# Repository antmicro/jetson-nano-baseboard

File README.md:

# Jetson Nano Baseboard

Copyright (c) 2020-2025 [Antmicro](https://www.antmicro.com)

## Overview

This project contains open hardware design files for a baseboard supporting the NVIDIA Jetson Nano, Xavier NX and TX2 NX SoMs.
It was created by [Antmicro](https://antmicro.com), a custom hardware, software and AI engineering company and NVIDIA's Jetson ecosystem partner.
The board can be interfaced with MIPI CSI-2 video devices through a unified Flexible Flat Cable (FFC) connector, supporting up to 4 sensors in a 2-lane configuration or 3 sensors in a 4-lane configuration.
Please refer to the Product Design Guide for the relevant SoM for more details regarding the supported CSI lane mappings.
You will find the SoM-related resources in NVIDIA's [Jetson Download Center](https://developer.nvidia.com/embedded/downloads). 

The design files for this project starting from Rev. 1.5 are provided and maintained in KiCad.
Older revisions of the board were prepared in Altium Designer and are kept on a separate [branch](https://github.com/antmicro/jetson-nano-baseboard/tree/1.4.7-altium).

### Project structure:

The main directory contains the KiCad design files, LICENSE and README.
The remaining files are stored in the following directories:

* ``img`` - contains graphics for this README
* ``linux-patches`` - contains patches which add camera support for camera modules from Allied Vision (see the BSP section below)

## Key features

* Jetson Nano / Xavier NX / TX2 NX SO-DIMM connector
* Gigabit Ethernet RJ45 connector
* Micro USB debug connector
* USB-C DFP (Host) port
* Micro HDMI video output interface
* Mini DisplayPort video output interface
* 2x 50-pin FFC connectors exposing up to 4 MIPI CSI-2 camera interfaces
* M.2 (key M) connector exposing PCIe x4 interface
* RTC battery backup
* EEPROM for storing board ID/SN
* 100x55mm (3.93 x 2.16 inch) mechanical outline 

## Getting started

The board can be produced and assembled using the provided design files.
Please take a look at the mechanical layers for more information regarding the PCB stackup recommended for fabrication.
The board can be powered by a voltage in the 6-36VDC range.
It is recommended to use a 12V 2A DC supply to power the board.
The board has an integrated power sequencer that starts the module automatically right after applying power supply.

### BSP

The baseboard's I/O interfaces are supported in the standard [Linux for Tegra (L4T) BSPs](https://developer.nvidia.com/embedded/linux-tegra) provided by NVIDIA for Jetson Nano / Xavier NX / TX2 NX. 
The BSP should work with the Open Source Jetson Baseboard out of the box.
However, to use the baseboard with various cameras and other accessories you may need to make modifications.
If you plan to use the board with Allied Vision [Alvium](https://www.alliedvision.com/en/products/embedded-vision-solutions/alvium-camera-modules-for-embedded-and-machine-vision-applications.html) image sensors, there is a ``linux-patches`` directory, which contains patch files that add support for the Allied Vision cameras for this baseboard with the Jetson Nano NX module.
The patches are named with the L4T release and can be applied to the corresponding branches of the Linux [repository](https://github.com/alliedvision/linux_nvidia_jetson) released by Allied Vision. 
Antmicro's services involve BSP development so you can hire us to make the necessary modifications for you.

You can use the USB OTG interface connector to upload a BSP image to a SoM inserted into the baseboard.

### Debug UART connection

Most of the debug messages are provided through the serial console.
The board includes an FTDI chip providing the UART interface to the host PC.
Please refer to the schematic sheets for more details.
The default debug UART channel is accessible through ``/dev/ttyUSB0`` (assuming that there are no other FTDI units connected to your PC).
The default baudrate for serial debug connection is 115200 baud with an 8-bit transmission, 1 stop bit and with no flow control.

### Revision info

1.5.x revision includes the design files converted into KiCad.
The BOM has been altered so the board can be produced despite the global chip shortage situation.
Revision 1.5.x changes the I2C multiplexer (PCA9548 -> PCA9547) used for handling the cameras and video accessories. 
You may need to adjust the devicetree entries for video accessories to make them work with the new I2C multiplexer chip.

## License

This project is licensed under the [Apache-2.0](LICENSE) license.

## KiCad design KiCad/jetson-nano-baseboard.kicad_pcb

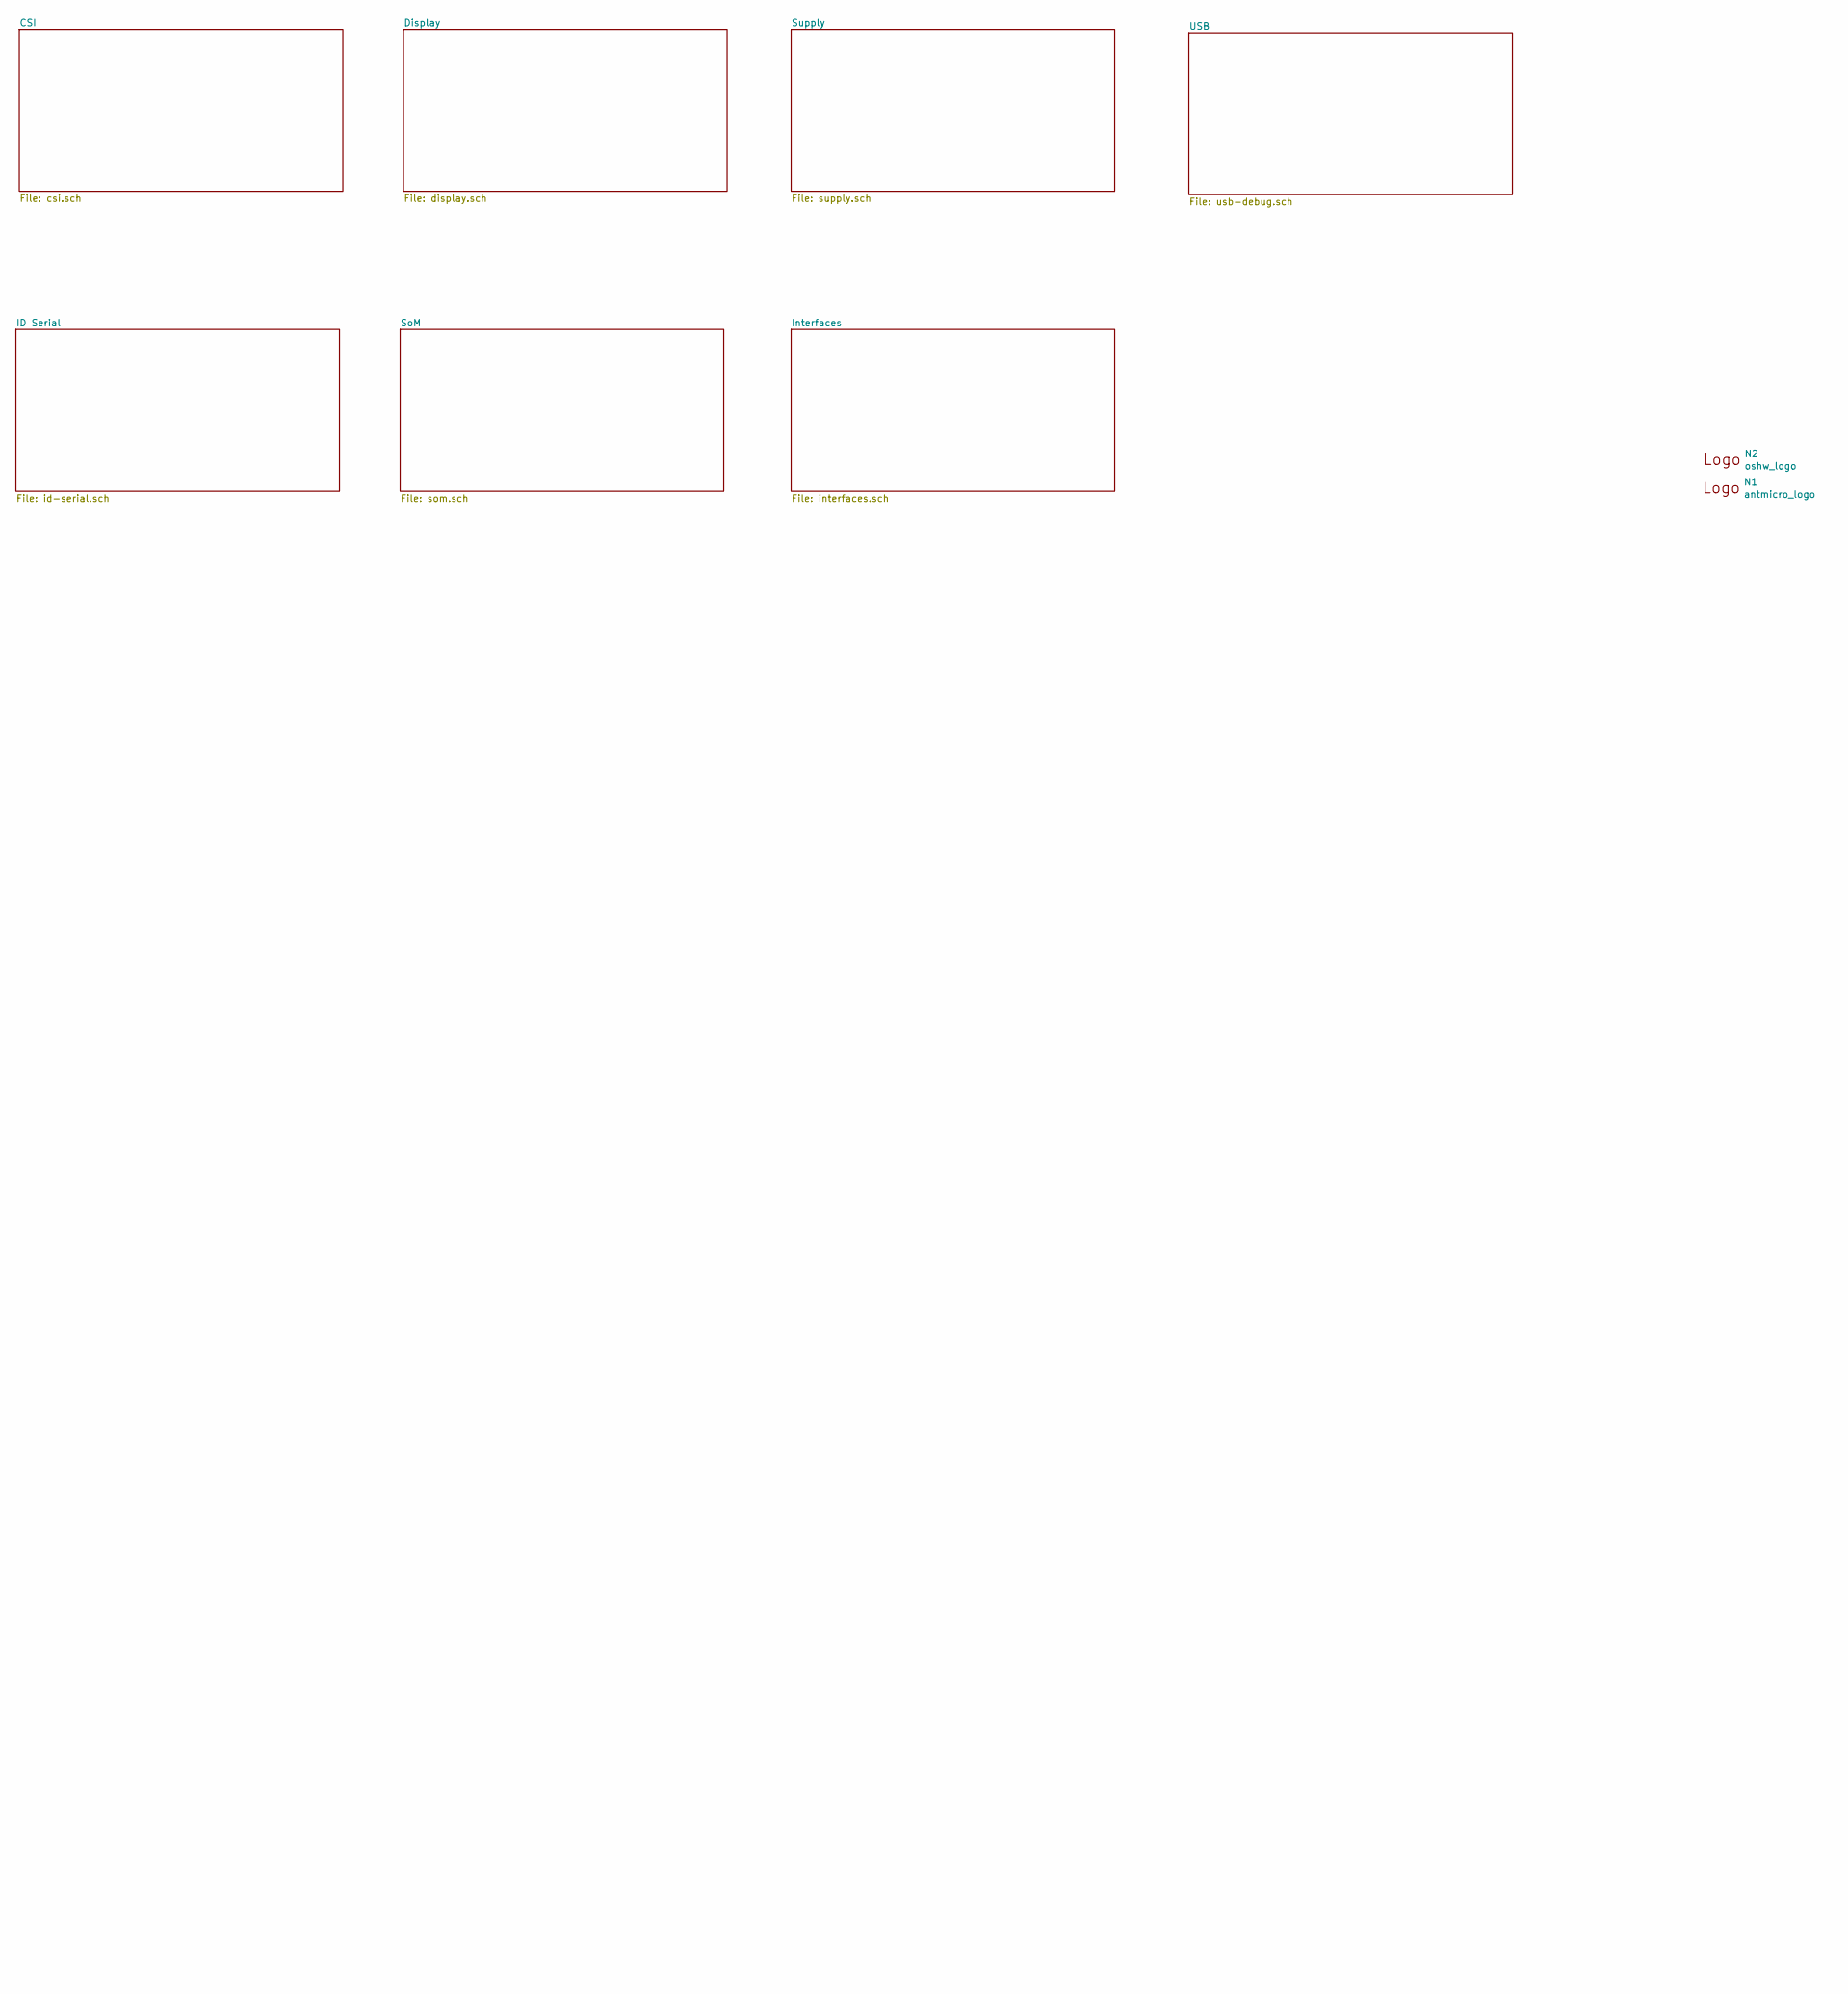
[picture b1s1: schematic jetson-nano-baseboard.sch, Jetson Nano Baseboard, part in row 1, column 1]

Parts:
N1: antmicro_logo; antmicro-logo_scaled_15mm
N2: oshw_logo; oshw-logo

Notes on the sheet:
Text

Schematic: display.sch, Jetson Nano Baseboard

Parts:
C1, C2, C3, C4: C_4u7_0402; 0402-cap; MPN GRM155R61A475MEAAD
C5, C6, C7, C8, C12, C26, C27, C39, C40, C42, C43, C44, C45, C73, C74, C75, C76, C77, C78, C79, C80: C_100n_0402; 0402-cap; MPN 0402X104K6R3CT
D2, D4: 1N4148WS; SOD-323; MPN 1N4148WS
D10, D11, D12: TPD2E009DBZR; SOT-23s; MPN TPD2E009DBZR
IC2, IC18: SON-15; PartSymbol TPD8S009DSMR
IC6: PCA9517ADP; MSOP-8; MPN PCA9517ADP
IC11: SN74LV1T125DCKR; SC70-5; MPN SN74LV1T125DCKR
J1: 685119136923; WE_685119136923; MPN 685119136923
J2: 2129320-3; MPN 2309413-1
L8, L9, L10: BLM18SG121TN1D; 0603; MPN BLM18SG121TN1D
M1: jetson-nano-connector; PartSymbol 2309413-1
R1, R2, R3, R4, R7, R8, R9, R10: R_5R6_0402; 0402-res; MPN ERJ2GEJ5R6X
R5, R6, R11, R37, R81, R83, R88: R_2k_0402; 0402-res; MPN CRCW04022K00FKED
R12, R82, R98, R99: R_0R_0402; 0402-res; MPN ERJ2GE0R00X
R26, R30, R100: R_100k_0402; 0402-res; MPN CRCW0402100KFKEDHP
R31, R32: R_1M0_0402; 0402-res; MPN CRG0402F1M0
T1: BSS138APW; SC70-3; MPN BSS138PW
TP2, TP13, TP14, TP25, TP26, TP33, TP34: TP-R-1.5; MPN N/A

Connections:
1V8_SYS: C5.1, IC11.5 (VCC), R88.1; also elsewhere on the board
3V3_SYS: C26.1, IC6.1 (VCCA), L10.1, R11.1, R81.1; also elsewhere on the board
5V0_SYS: IC2.13 (VCC), IC2.15 (VCC), L9.1; also elsewhere on the board
/Display/DP_CEC: J2.6 (CONFIG2), R32.2
/Display/DP_HPD: IC11.4 (Y), M1.88 (DP0_HPD)
/Display/DP_HPD_IN: D12.2 (IO2), IC11.2 (A), J2.2 (HOTPLUG), R100.2
/Display/DP_MODE: J2.4 (CONFIG1), R31.2
/Display/EDP0_TX_N: C40.1, M1.39 (DP0_TXD0_N)
/Display/EDP0_TX_P: C39.1, M1.41 (DP0_TXD0_P)
/Display/EDP1_TX_N: C43.1, M1.45 (DP0_TXD1_N)
/Display/EDP1_TX_P: C42.1, M1.47 (DP0_TXD1_P)
/Display/EDP2_TX_N: C7.1, M1.51 (DP0_TXD2_N)
/Display/EDP2_TX_P: C6.1, M1.53 (DP0_TXD2_P)
/Display/EDP3_TX_N: C12.1, M1.57 (DP0_TXD3_N)
/Display/EDP3_TX_P: C8.1, M1.59 (DP0_TXD3_P)
/Display/EDP_AUX_N: C45.1, M1.90 (DP0_AUX_N)
/Display/EDP_AUX_P: C44.1, M1.92 (DP0_AUX_P)
/Display/EDP_C_AUX_C_N: C45.2, J2.18 (AUX_CH_N), R26.1
/Display/EDP_C_AUX_C_P: C44.2, J2.16 (AUX_CH_P), R30.2
/Display/ML_C_LANE0_N: C40.2, IC2.3 (D0-), J2.5 (ML_LANE0_N)
/Display/ML_C_LANE0_P: C39.2, IC2.1 (D0+), J2.3 (ML_LANE0_P)
/Display/ML_C_LANE1_N: C43.2, IC2.6 (D1-), J2.11 (ML_LANE1_N)
/Display/ML_C_LANE1_P: C42.2, IC2.4 (D1+), J2.9 (ML_LANE1_P)
/Display/ML_C_LANE2_N: C7.2, IC2.9 (D2-), J2.17 (ML_LANE2_N)
/Display/ML_C_LANE2_P: C6.2, IC2.7 (D2+), J2.15 (ML_LANE2_P)
/Display/ML_C_LANE3_N: C12.2, IC2.12 (D3-), J2.12 (ML_LANE3_N)
/Display/ML_C_LANE3_P: C8.2, IC2.10 (D3+), J2.10 (ML_LANE3_P)
/Display/TMDS_C1_CLK_N: C80.2, IC18.12 (D3-), R10.1
/Display/TMDS_C1_CLK_P: C78.2, IC18.10 (D3+), R9.1
/Display/TMDS_C1_D0_N: C79.2, IC18.9 (D2-), R8.1
/Display/TMDS_C1_D0_P: C76.2, IC18.7 (D2+), R7.1
/Display/TMDS_C1_D1_N: C77.2, IC18.6 (D1-), R4.1
/Display/TMDS_C1_D1_P: C75.2, IC18.4 (D1+), R3.1
/Display/TMDS_C1_D2_N: C74.2, IC18.3 (D0-), R2.1
/Display/TMDS_C1_D2_P: C73.2, IC18.1 (D0+), R1.1
/Display/TMDS_CEC: M1.94 (HDMI_CEC), TP26.1
/Display/TMDS_CEC_IN: D11.2 (IO2), J1.14 (CEC), R37.1
/Display/TMDS_CLK_C_N: J1.12 (TMDSClock-), R10.2
/Display/TMDS_CLK_C_P: J1.11 (TMDSClock+), R9.2
/Display/TMDS_CLK_N: C80.1, M1.81 (DP1_TXD3_N)
/Display/TMDS_CLK_P: C78.1, M1.83 (DP1_TXD3_P)
/Display/TMDS_D0_C_N: J1.9 (TMDSData0-), R8.2
/Display/TMDS_D0_C_P: J1.8 (TMDSData0+), R7.2
/Display/TMDS_D0_N: C79.1, M1.75 (DP1_TXD2_N)
/Display/TMDS_D0_P: C76.1, M1.77 (DP1_TXD2_P)
/Display/TMDS_D1_C_N: J1.6 (TMDSData1-), R4.2
/Display/TMDS_D1_C_P: J1.5 (TMDSData1+), R3.2
/Display/TMDS_D1_N: C77.1, M1.69 (DP1_TXD1_N)
/Display/TMDS_D1_P: C75.1, M1.71 (DP1_TXD1_P)
/Display/TMDS_D2_C_N: J1.3 (TMDSData2-), R2.2
/Display/TMDS_D2_C_P: J1.2 (TMDSData2+), R1.2
/Display/TMDS_D2_N: C74.1, M1.63 (DP1_TXD0_N)
/Display/TMDS_D2_P: C73.1, M1.65 (DP1_TXD0_P)
/Display/TMDS_HPD_IN: D11.1 (IO1), J1.19 (HotPlugDetect/HEAC-), R82.1
/Display/TMDS_SCL: M1.100 (DP1_AUX_P), R98.2, TP33.1
/Display/TMDS_SCL_5V0: D10.2 (IO2), IC6.7 (SCLB), J1.15 (SCL), R5.2
/Display/TMDS_SDA: M1.98 (DP1_AUX_N), R99.2, TP34.1
/Display/TMDS_SDA_5V0: D10.1 (IO1), IC6.6 (SDAB), J1.16 (SDA), R6.2
DP_PWR: D2.A, L10.2, R26.2
HDMI_PWR: C27.2, D4.A, IC6.5 (EN), IC6.8 (VCCB), IC18.13 (VCC), IC18.15 (VCC), L9.2, R5.1, R6.1
HDMI_SHIELD: J1.1 (TMDSData2Shield), J1.4 (TMDSData1Shield), J1.7 (TMDSData0Shield), J1.10 (TMDSClockShield), J1.Shell (Shield), L8.2
M2_ALERT: M1.212 (GPIO10), TP2.1; also elsewhere on the board
unnamed: C1.2, C2.2, D4.C, J1.18 (+5VPower)
unnamed: C3.2, C4.2, D2.C, J2.20 (DP_PWR)
unnamed: IC6.2 (SCLA), R81.2, R98.1
unnamed: IC6.3 (SDAA), R11.2, R99.1
unnamed: J1.13 (DDC/CECGround/HEACShield), R12.2
unnamed: M1.206 (GPIO07), TP13.1
unnamed: M1.218 (GPIO12), TP14.1
unnamed: R82.2, R83.1, T1.1 (G)
OTG_USB_VBUS: M1.87 (GPIO00); also elsewhere on the board
TMDS_HPD: M1.96 (DP1_HPD), R88.2, T1.3 (D), TP25.1

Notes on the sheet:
HDMI Interface
5V0
3V3
DDC/HPD
Text
Display
DisplayPort Interface
1V8

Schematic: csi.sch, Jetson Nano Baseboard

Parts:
C9: C_100n_0402; 0402-cap; MPN 0402X104K6R3CT
IC1: TCA9548ARGER; VQFN-24; MPN TCA9548ARGER
J6: WE_68715014522; WE_68715014522_ONE-SIDE; MPN 68715014522
J7: WE_68715014022; MPN 68715014022
M1: jetson-nano-connector; PartSymbol 2309413-1
R13, R15, R17, R19, R21, R23, R39, R57, R58, R59, R60, R61, R78, R79, R80: R_0R_0402; 0402-res; MPN ERJ2GE0R00X
R18, R22, R24, R25, R27, R28, R29, R33, R34, R35: R_2k_0402; 0402-res; MPN CRCW04022K00FKED
TP1, TP3, TP4, TP6, TP9, TP10, TP11, TP12: TP-R-1.5; MPN N/A

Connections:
1V8_SYS: R23.2, R79.2; also elsewhere on the board
3V3_FFC1: J6.47, J6.48, R78.2; also elsewhere on the board
3V3_FFC2: J7.47, J7.48, R80.2; also elsewhere on the board
3V3_SYS: C9.1, IC1.21 (VCC), R34.1, R35.1, R39.2; also elsewhere on the board
5V0_SYS: J6.49, J6.50, J7.49, J7.50; also elsewhere on the board
/CSI/CAM0_SCL: J6.40, R15.1, R24.2
/CSI/CAM0_SDA: J6.39, R13.1, R25.2
/CSI/CAM1_SCL: J6.42, R18.2, R21.1
/CSI/CAM1_SDA: J6.41, R17.1, R22.2
/CSI/CAM2_SCL: J7.42, R27.2, R58.1
/CSI/CAM2_SDA: J7.41, R19.1, R28.2
/CSI/CAM3_SCL: J7.40, R33.2, R61.1
/CSI/CAM3_SDA: J7.39, R29.2, R59.1
/CSI/CAM_I2C_SCL: M1.213 (CAM_I2C_SCL), R35.2, R60.2, TP10.1
/CSI/CAM_I2C_SDA: M1.215 (CAM_I2C_SDA), R34.2, R57.2, TP1.1
/CSI/CSI_A_CLK_N: J7.28, M1.10 (CSI0_CLK_N)
/CSI/CSI_A_CLK_P: J7.29, M1.12 (CSI0_CLK_P)
/CSI/CSI_A_D0_N: J7.25, M1.4 (CSI0_D0_N)
/CSI/CSI_A_D0_P: J7.26, M1.6 (CSI0_D0_P)
/CSI/CSI_A_D1_N: J7.23, M1.16 (CSI0_D1_N)
/CSI/CSI_A_D1_P: J7.24, M1.18 (CSI0_D1_P)
/CSI/CSI_B_D0_N: J7.21, M1.3 (CSI1_D0_N)
/CSI/CSI_B_D0_P: J7.22, M1.5 (CSI1_D0_P)
/CSI/CSI_B_D1_N: J7.19, M1.15 (CSI1_D1_N)
/CSI/CSI_B_D1_P: J7.20, M1.17 (CSI1_D1_P)
/CSI/CSI_C_CLK_N: J7.10, M1.52 (CSI4_CLK_N)
/CSI/CSI_C_CLK_P: J7.11, M1.54 (CSI4_CLK_P)
/CSI/CSI_C_D0_N: J7.7, M1.46 (CSI4_D0_N)
/CSI/CSI_C_D0_P: J7.8, M1.48 (CSI4_D0_P)
/CSI/CSI_C_D1_N: J7.5, M1.58 (CSI4_D1_N)
/CSI/CSI_C_D1_P: J7.6, M1.60 (CSI4_D1_P)
/CSI/CSI_D_D0_N: J7.3, M1.40 (CSI4_D2_N)
/CSI/CSI_D_D0_P: J7.4, M1.42 (CSI4_D2_P)
/CSI/CSI_D_D1_N: J7.1, M1.64 (CSI4_D3_N)
/CSI/CSI_D_D1_P: J7.2, M1.66 (CSI4_D3_P)
/CSI/CSI_E_CLK_N: J6.28, M1.28 (CSI2_CLK_N)
/CSI/CSI_E_CLK_P: J6.29, M1.30 (CSI2_CLK_P)
/CSI/CSI_E_D0_N: J6.25, M1.22 (CSI2_D0_N)
/CSI/CSI_E_D0_P: J6.26, M1.24 (CSI2_D0_P)
/CSI/CSI_E_D1_N: J6.23, M1.34 (CSI2_D1_N)
/CSI/CSI_E_D1_P: J6.24, M1.36 (CSI2_D1_P)
/CSI/CSI_F_CLK_N: M1.27 (CSI3_CLK_N)
/CSI/CSI_F_CLK_P: M1.29 (CSI3_CLK_P)
/CSI/CSI_F_D0_N: J6.21, M1.21 (CSI3_D0_N)
/CSI/CSI_F_D0_P: J6.22, M1.23 (CSI3_D0_P)
/CSI/CSI_F_D1_N: J6.19, M1.33 (CSI3_D1_N)
/CSI/CSI_F_D1_P: J6.20, M1.35 (CSI3_D1_P)
/CSI/CSI_G_CLK_N: J6.10, M1.76 (DSI_CLK_N)
/CSI/CSI_G_CLK_P: J6.11, M1.78 (DSI_CLK_P)
/CSI/CSI_G_D0_N: J6.7, M1.70 (DSI_D0_N)
/CSI/CSI_G_D0_P: J6.8, M1.72 (DSI_D0_P)
/CSI/CSI_G_D1_N: J6.5, M1.82 (DSI_D1_N)
/CSI/CSI_G_D1_P: J6.6, M1.84 (DSI_D1_P)
unnamed: IC1.1 (SD0), R13.2
unnamed: IC1.2 (SC0), R15.2
unnamed: IC1.3 (SD1), R17.2
unnamed: IC1.4 (SC1), R21.2
unnamed: IC1.5 (SD2), R19.2
unnamed: IC1.6 (SC2), R58.2
unnamed: IC1.7 (SD3), R59.2
unnamed: IC1.8 (SC3), R61.2
unnamed: IC1.10 (SD4), TP11.1
unnamed: IC1.11 (SC4), TP12.1
unnamed: IC1.19 (SCL), R60.1
unnamed: IC1.20 (SDA), R57.1
unnamed: IC1.24 (~RESET), R39.1
unnamed: M1.9 ((CSI1_CLK)RSVD), TP3.1
unnamed: M1.11 ((CSI1_CLK)RSVD), TP4.1
unnamed: M1.118 (GPIO01), TP9.1
unnamed: M1.120 (CAM1_PWDN), TP6.1
unnamed: R18.1, R22.1, R23.1, R24.1, R25.1, R78.1
unnamed: R27.1, R28.1, R29.1, R33.1, R79.1, R80.1
VSYNC_CAM1_1: J6.32; also elsewhere on the board
VSYNC_CAM1_2: J6.34; also elsewhere on the board
VSYNC_CAM2_1: J7.32, M1.114 (CAM0_PWDN)
VSYNC_CAM2_2: J7.34; also elsewhere on the board

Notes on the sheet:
CAM_L_D3_N
CAM_L_D3_P
CAM_L_D2_N
CAM_L_D2_P
CAM_L_D1_N
CAM_L_D1_P
CAM_L_D0_N
CAM_L_D0_P
CAM_L_SDA
CAM_L_SCL
CAM_R_SDA
CAM_R_SCL
CAM_L_CLK_N
CAM_L_CLK_P
LEFT CAMERA
CAM_R_D3_N
CAM_R_D3_P
CAM_R_D2_N
CAM_R_D2_P
CAM_R_D1_N
CAM_R_D1_P
CAM_R_D0_N
CAM_R_D0_P
CAM_R_CLK_N
CAM_R_CLK_P
RIGHT CAMERA
Camera FFC #1
Camera FFC #2
0x70h
0b1110000R
I2C address:
SoM interface
Text
Camera I2C multiplexer
Camera Interfaces

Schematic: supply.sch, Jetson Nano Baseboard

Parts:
C16, C17, C18: C_47u_0805; 0805-cap; MPN C0805C476M9PACTU
C19, C71: C_100n_0402; 0402-cap; MPN 0402X104K6R3CT
C21, C22, C23: C_2u2_1206; 1206-cap; MPN C1206C225M4VACTU
C24: C_10n_0402; 0402-cap; MPN 04025G103ZAT2A
C25: C_4n7_0402; 0402-cap; MPN CGA2B3X7S2A472K050BB
C28: C_1u_0402; 0402-cap; MPN C1005X6S1A105K050BC
C41: C_47n_0402; 0402-cap; MPN MC0402X473K160CT
C55, C57, C59, C65: C_2u2_0402; 0402-cap; MPN C1005X5R1A225K050BC
C56, C58, C60, C63: C_10u_0603; 0603-cap; MPN GRM188R61A106KE69D
C61: C_100p_0402; 0402-cap; MPN 0402N101J500CT
C64: C_47p_0402; 0402-cap; MPN C0402C470J5GACTU
D1: PDS760-13; PowerDI; MPN PDS760-13
D13, D14: 1N4148WS; SOD-323; MPN 1N4148WS
FAN1: molex_2223-2021; MPN 2223-2021
IC3: TPS54561; WSON-10_4x4; MPN TPS54561-Q1
IC4: TLV70018DCKT; SC70-5; MPN TLV70018DCKT
IC8, IC9: LM3671MF-3.3; SOT23-5N; MPN LM3671MF-3.3/NOPB
IC10: TPS62823DLCT; TPS62823; MPN TPS62823DLCT
IC12: 74HC00PW; TSSOP-14; MPN 74HC00PW
IC13: SN74LVC1G126DCKR; R-PDSO-G5; MPN SN74LVC1G126DCKR
J4: DC_SOCKET; MPN MJ-179PH
L1: WE_7447798720; MPN 7447798720
L4, L6: LQH32PN2R2NN0L; MPN LQH32PN2R2NN0L
L5: IHLP1212AEERR47M11; IHLP-1212AE; MPN IHLP1212AEERR47M11
R16, R36, R87: R_1k_0402; 0402-res; MPN CR0402-FX-1001GLF
R44, R134: R_243k_0402; 0402-res; MPN MCMR04X2433FTL
R45: R_49R9_0402; 0402-res; MPN CRCW040249R9FKED
R46, R135: R_53k6_0402; 0402-res; MPN CPF0402B53K6E1
R48: R_16k9_0402; 0402-res; MPN ERA2AEB1692X
R52: R_10k2_0402; 0402-res; MPN MCWR04X1022FTL
R75, R89, R91, R92, R130: R_0R_0402; 0402-res; MPN ERJ2GE0R00X
R76, R90, R93, R94, R95, R96: R_10k_0402; 0402-res; MPN CRCW040210K0FKEDHP
R77: R_100k_0402; 0402-res; MPN CRCW0402100KFKEDHP
R84, R86: R_200k_0402; 0402-res; MPN RC0402FR-07200KL
R85: R_470k_0402; 0402-res; MPN RC0402FR-07470KL
T3: BSS138APW; SC70-3; MPN BSS138PW
TP5, TP16, TP17, TP40, TP41, TP42, TP43, TP44, TP45, TP47: TP-R-1.5; MPN N/A

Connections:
1V8_SYS: C28.2, IC4.5 (VOUT), TP47.1; also elsewhere on the board
3V3_FFC1: C58.2, IC9.4 (FB), L6.2, TP45.1; also elsewhere on the board
3V3_FFC2: C56.2, IC8.4 (FB), L4.2, TP43.1; also elsewhere on the board
3V3_SYS: C60.2, C61.2, L5.2, R134.1, TP41.1; also elsewhere on the board
5V0_SYS: C16.2, C17.2, C18.2, C55.2, C57.2, C59.2, C65.2, C71.2, D14.C, FAN1.1, IC4.1 (VIN), IC8.1 (VIN), IC9.1 (VIN), IC10.7 (VIN), IC12.14 (VCC), IC13.1 (OE), IC13.5 (VCC), L1.2, R16.1, R36.1, R45.2, R75.2, R77.2, R84.2, R86.2, R89.2, R91.2, R92.1, TP42.1; also elsewhere on the board
#MOD_SLEEP: R95.2; also elsewhere on the board
#RESET: R76.2, R90.2, R93.2, R94.2, R96.2; also elsewhere on the board
#SHUTDOWN_REQ: IC12.4 (2A), R86.1; also elsewhere on the board
/Supply/Q: D13.C, IC12.3 (~1Y), IC12.5 (2B), R36.2, R85.1
/Supply/QDEL: C63.2, D13.A, IC12.12 (4A), IC12.13 (4B), IC13.2 (A), R85.2, R87.2
/Supply/\~PWR_SET~: C41.2, IC12.1 (1A), R84.1
unnamed: C19.1, IC3.1 (BOOT)
unnamed: C19.2, D1.C, IC3.9 (SW), L1.1
unnamed: C24.1, IC3.4 (SS/TR)
unnamed: C25.2, R48.1
unnamed: C61.1, IC10.2 (FB), R134.2, R135.2
unnamed: C64.2, IC3.7 (COMP), R48.2
unnamed: D14.A, FAN1.2, T3.3 (D)
unnamed: IC3.3 (EN), TP5.1
unnamed: IC3.5 (RT/CLK), R44.1
unnamed: IC3.6 (FB), R46.1, R52.2
unnamed: IC4.3 (EN), R92.2, R94.1
unnamed: IC8.3 (RUN), R89.1, R90.1
unnamed: IC8.6 (SW), L4.1
unnamed: IC9.3 (RUN), R91.1, R93.1
unnamed: IC9.6 (SW), L6.1
unnamed: IC10.1 (EN), R75.1, R76.1
unnamed: IC10.6 (SW), L5.1
unnamed: IC12.2 (1B), IC12.6 (~2Y), R16.2
unnamed: IC12.8 (~3Y), R130.2
unnamed: IC12.9 (3A), IC12.10 (3B), IC12.11 (~4Y)
unnamed: R45.1, R46.2
unnamed: R95.1, R96.1, T3.1 (G)
PWR_EN: IC13.4 (Y), R130.1; also elsewhere on the board
PWR_GOOD: IC3.10 (PWRGD), R77.1, R87.1, TP40.1; also elsewhere on the board
VIN: C21.2, C22.2, C23.2, IC3.2 (VDD), J4.1, TP16.1

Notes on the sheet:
Text
Power input
9...36 VDC
Main DC/DC
Power sequencer
System 3V3
Camera #2 3V3
Camera #1 3V3
System 1V8
FAN 5V
#RESET - fan off only in shutdown
#PWR_RST
Power Supply
Bulk load
5V/5A
TODO: change into locking one

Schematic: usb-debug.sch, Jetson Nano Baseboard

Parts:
C15, C29: C_47p_0402; 0402-cap; MPN C0402C470J5GACTU
C30, C33, C48, C50, C53, C54, C72: C_100n_0402; 0402-cap; MPN 0402X104K6R3CT
C31: 100u; 1206; Voltage 6.3V; MPN C1206C107M9PACTU
C32, C66: C_1u_0402; 0402-cap; MPN C1005X6S1A105K050BC
C34: C_47u_0805; 0805-cap; MPN C0805C476M9PACTU
C35: C_10u_0603; 0603-cap; MPN GRM188R61A106KE69D
C62: C_4u7_0402; 0402-cap; MPN GRM155R61A475MEAAD
C67: C_2u2_0402; 0402-cap; MPN C1005X5R1A225K050BC
D3, D5, D8, D9: TPD2E009DBZR; SOT-23s; MPN TPD2E009DBZR
D6, D7: TPD4E05U06_PASS; PartSymbol TPD4E05U06DQAR
D17: 1N4148WS; SOD-323; MPN 1N4148WS
IC5: QFN-32; PartNumber FT232RQ
IC7: HD3SS3220; RNH0030A; MPN HD3SS3220RNHT
IC15: TLV70018DCKT; SC70-5; MPN TLV70018DCKT
IC16: NCP380HSNAJAAT1G; TSOP-6; MPN NCP380HSNAJAAT1G
J5, J9: CON-Molex-047346-0001; PartSymbol 47346-0001
J11: 632723300011; WE_632723300011; MPN 632723300011
L2, L3: BLM18EG221SN1D; 0603; MPN BLM18EG221SN1D
L7: BLM18SG121TN1D; 0603; MPN BLM18SG121TN1D
LED1: LED0603; MPN KPT-1608SGC
Q1: PMV32UP; SOT-23s; MPN PMV32UP
R20, R41: R_22R_0402; 0402-res; MPN CRCW040222R0FKED
R42, R47, R49, R56, R62, R63, R64, R65, R66, R68, R71, R103, R104, R105, R106, R107, R108, R109, R110: R_0R_0402; 0402-res; MPN ERJ2GE0R00X
R43: R_470R_0402; 0402-res; MPN CRCW0402470RFKED
R50: 10k2; 0402; MPN CPF0402B10K2E1
R51: R_909k_0402; 0402-res; MPN ERJ2RKF9093X
R53, R67: R_200k_0402; 0402-res; MPN RC0402FR-07200KL
R54, R72, R102, R131: R_10k_0402; 0402-res; MPN CRCW040210K0FKEDHP
R55, R69, R70, R73: R_2k_0402; 0402-res; MPN CRCW04022K00FKED
R101: R_100k_0402; 0402-res; MPN CRCW0402100KFKEDHP
T6: BSS138APW; SC70-3; MPN BSS138PW
TP18, TP19, TP21, TP22, TP32: TP-R-1.5; MPN N/A

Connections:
1V8_DBG: C66.2, IC5.1 (VCCIO), IC15.5 (VOUT)
3V3_SYS: C33.1, IC7.8 (VCC33), R53.2, R69.1, R70.1; also elsewhere on the board
5V0_DBG: C67.2, C72.2, D17.C, IC5.19 (VCC), IC15.1 (VIN), IC15.3 (EN), L3.2
5V0_SYS: C32.2, C34.2, D17.A, IC7.30 (VDD5), IC16.1 (IN), Q1.2 (S), R42.1, R43.2, R47.2, R54.1, R55.1, R67.2, R71.1, R101.2; also elsewhere on the board
/USB/CC1: IC7.2 (CC1), R63.1, R66.2
/USB/CC2: IC7.1 (CC2), R64.1, R65.2
/USB/C_CC1: D5.2 (IO2), J11.A5 (CC1), R63.2, R64.2
/USB/C_CC2: D5.1 (IO1), J11.B5 (CC2), R65.1, R66.1
/USB/C_USBSS_RX1_N: D6.1 (CH1), J11.B10 (SSRXn1), R104.2
/USB/C_USBSS_RX1_P: D6.2 (CH2), J11.B11 (SSRXp1), R106.2
/USB/C_USBSS_RX2_N: D7.5 (CH4), J11.A10 (SSRXn2), R109.2
/USB/C_USBSS_RX2_P: D7.4 (CH3), J11.A11 (SSRXp2), R110.2
/USB/C_USBSS_RX6_N: IC7.10 (RXn), R108.2
/USB/C_USBSS_RX6_P: IC7.9 (RXp), R107.2
/USB/C_USBSS_TX1_N: C48.1, D6.5 (CH4), J11.A3 (SSTXn1)
/USB/C_USBSS_TX1_P: C50.1, D6.4 (CH3), J11.A2 (SSTXp1)
/USB/C_USBSS_TX2_N: C53.1, D7.2 (CH2), J11.B3 (SSTXn2)
/USB/C_USBSS_TX2_P: C54.1, D7.1 (CH1), J11.B2 (SSTXp2)
/USB/C_USBSS_TX6_N: IC7.7 (TXn), R105.2
/USB/C_USBSS_TX6_P: IC7.6 (TXp), R103.2
/USB/DBG_USB_D_N: C29.2, D3.1 (IO1), IC5.15 (USBDN), J9.2 (D-)
/USB/DBG_USB_D_P: C15.2, D3.2 (IO2), IC5.14 (USBDP), J9.3 (D+)
/USB/EN_MUX: IC7.12 (ENn_MUX), R56.2, R68.1
/USB/USBC_ADDR: IC7.22 (ADDR), TP21.1
/USB/USBC_FAULT: IC7.24 (VCONN_FAULT_N), TP32.1
/USB/USBC_ID: IC7.27 (ID), Q1.1 (G), R68.2, R101.1, TP18.1
/USB/USBC_INTN: IC7.23 (INT_N/OUT3), R67.1
/USB/USBC_SCL: IC7.26 (SCL/OUT2), R70.2
/USB/USBC_SDA: IC7.25 (SDA/OUT1), R69.2
/USB/USBSS_RX1_N: IC7.14 (RX1n), R104.1
/USB/USBSS_RX1_P: IC7.15 (RX1p), R106.1
/USB/USBSS_RX2_N: IC7.18 (RX2n), R109.1
/USB/USBSS_RX2_P: IC7.19 (RX2p), R110.1
/USB/USBSS_TX1_N: C48.2, IC7.16 (TX1n)
/USB/USBSS_TX1_P: C50.2, IC7.17 (TX1p)
/USB/USBSS_TX2_N: C53.2, IC7.20 (TX2n)
/USB/USBSS_TX2_P: C54.2, IC7.21 (TX2p)
unnamed: C30.2, IC5.16 (3V3OUT)
unnamed: C31.2, IC16.6 (OUT), L2.1
unnamed: C62.2, D9.1 (IO1), D9.2 (IO2), J5.1 (VCC), R71.2, R72.1
unnamed: IC5.2 (RXD), R41.1
unnamed: IC5.30 (TXD), R20.1
unnamed: IC7.3 (CURRENT_MODE), R54.2
unnamed: IC7.4 (PORT), R55.2
unnamed: IC7.5 (VBUS_DET), R51.1
unnamed: IC7.11 (DIR), R53.1
unnamed: IC7.29 (ENn_CC), R62.2
unnamed: IC16.3 (EN), R47.1, R49.2, R102.2
unnamed: IC16.4 (~FLAG), LED1.K
unnamed: IC16.5 (ILIM), R50.2
unnamed: J5.4 (ID), TP22.1
unnamed: J9.1 (VCC), L3.1
unnamed: J11.B8 (SBU2), TP19.1
unnamed: LED1.A, R43.1
unnamed: Q1.3 (D), R49.1
unnamed: R72.2, R73.1, T6.1 (G)
OTG_USB_D_N: D8.1 (IO1), J5.2 (D-); also elsewhere on the board
OTG_USB_D_P: D8.2 (IO2), J5.3 (D+); also elsewhere on the board
OTG_USB_VBUS: T6.3 (D); also elsewhere on the board
UART1_RX: R20.2; also elsewhere on the board
UART1_TX: R41.2; also elsewhere on the board
USB1_D_N: J11.A7 (Dn1), J11.B7 (Dn2); also elsewhere on the board
USB1_D_P: J11.A6 (Dp1), J11.B6 (Dp2); also elsewhere on the board
USBC_VBUS: C35.2, J11.A4 (VBUS), J11.A9 (VBUS), J11.B4 (VBUS), J11.B9 (VBUS), L2.2, R42.2, R51.2, R131.2
USBSS_RX6_N: R108.1; also elsewhere on the board
USBSS_RX6_P: R107.1; also elsewhere on the board
USBSS_TX6_N: R105.1; also elsewhere on the board
USBSS_TX6_P: R103.1; also elsewhere on the board

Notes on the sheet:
Text
Debug USB connector
Debug UART
Current limit set to 2.1A
USB Load Switch
USB_PW
USB-OTG
USB-C Multiplexer
USB-C Connector
USB

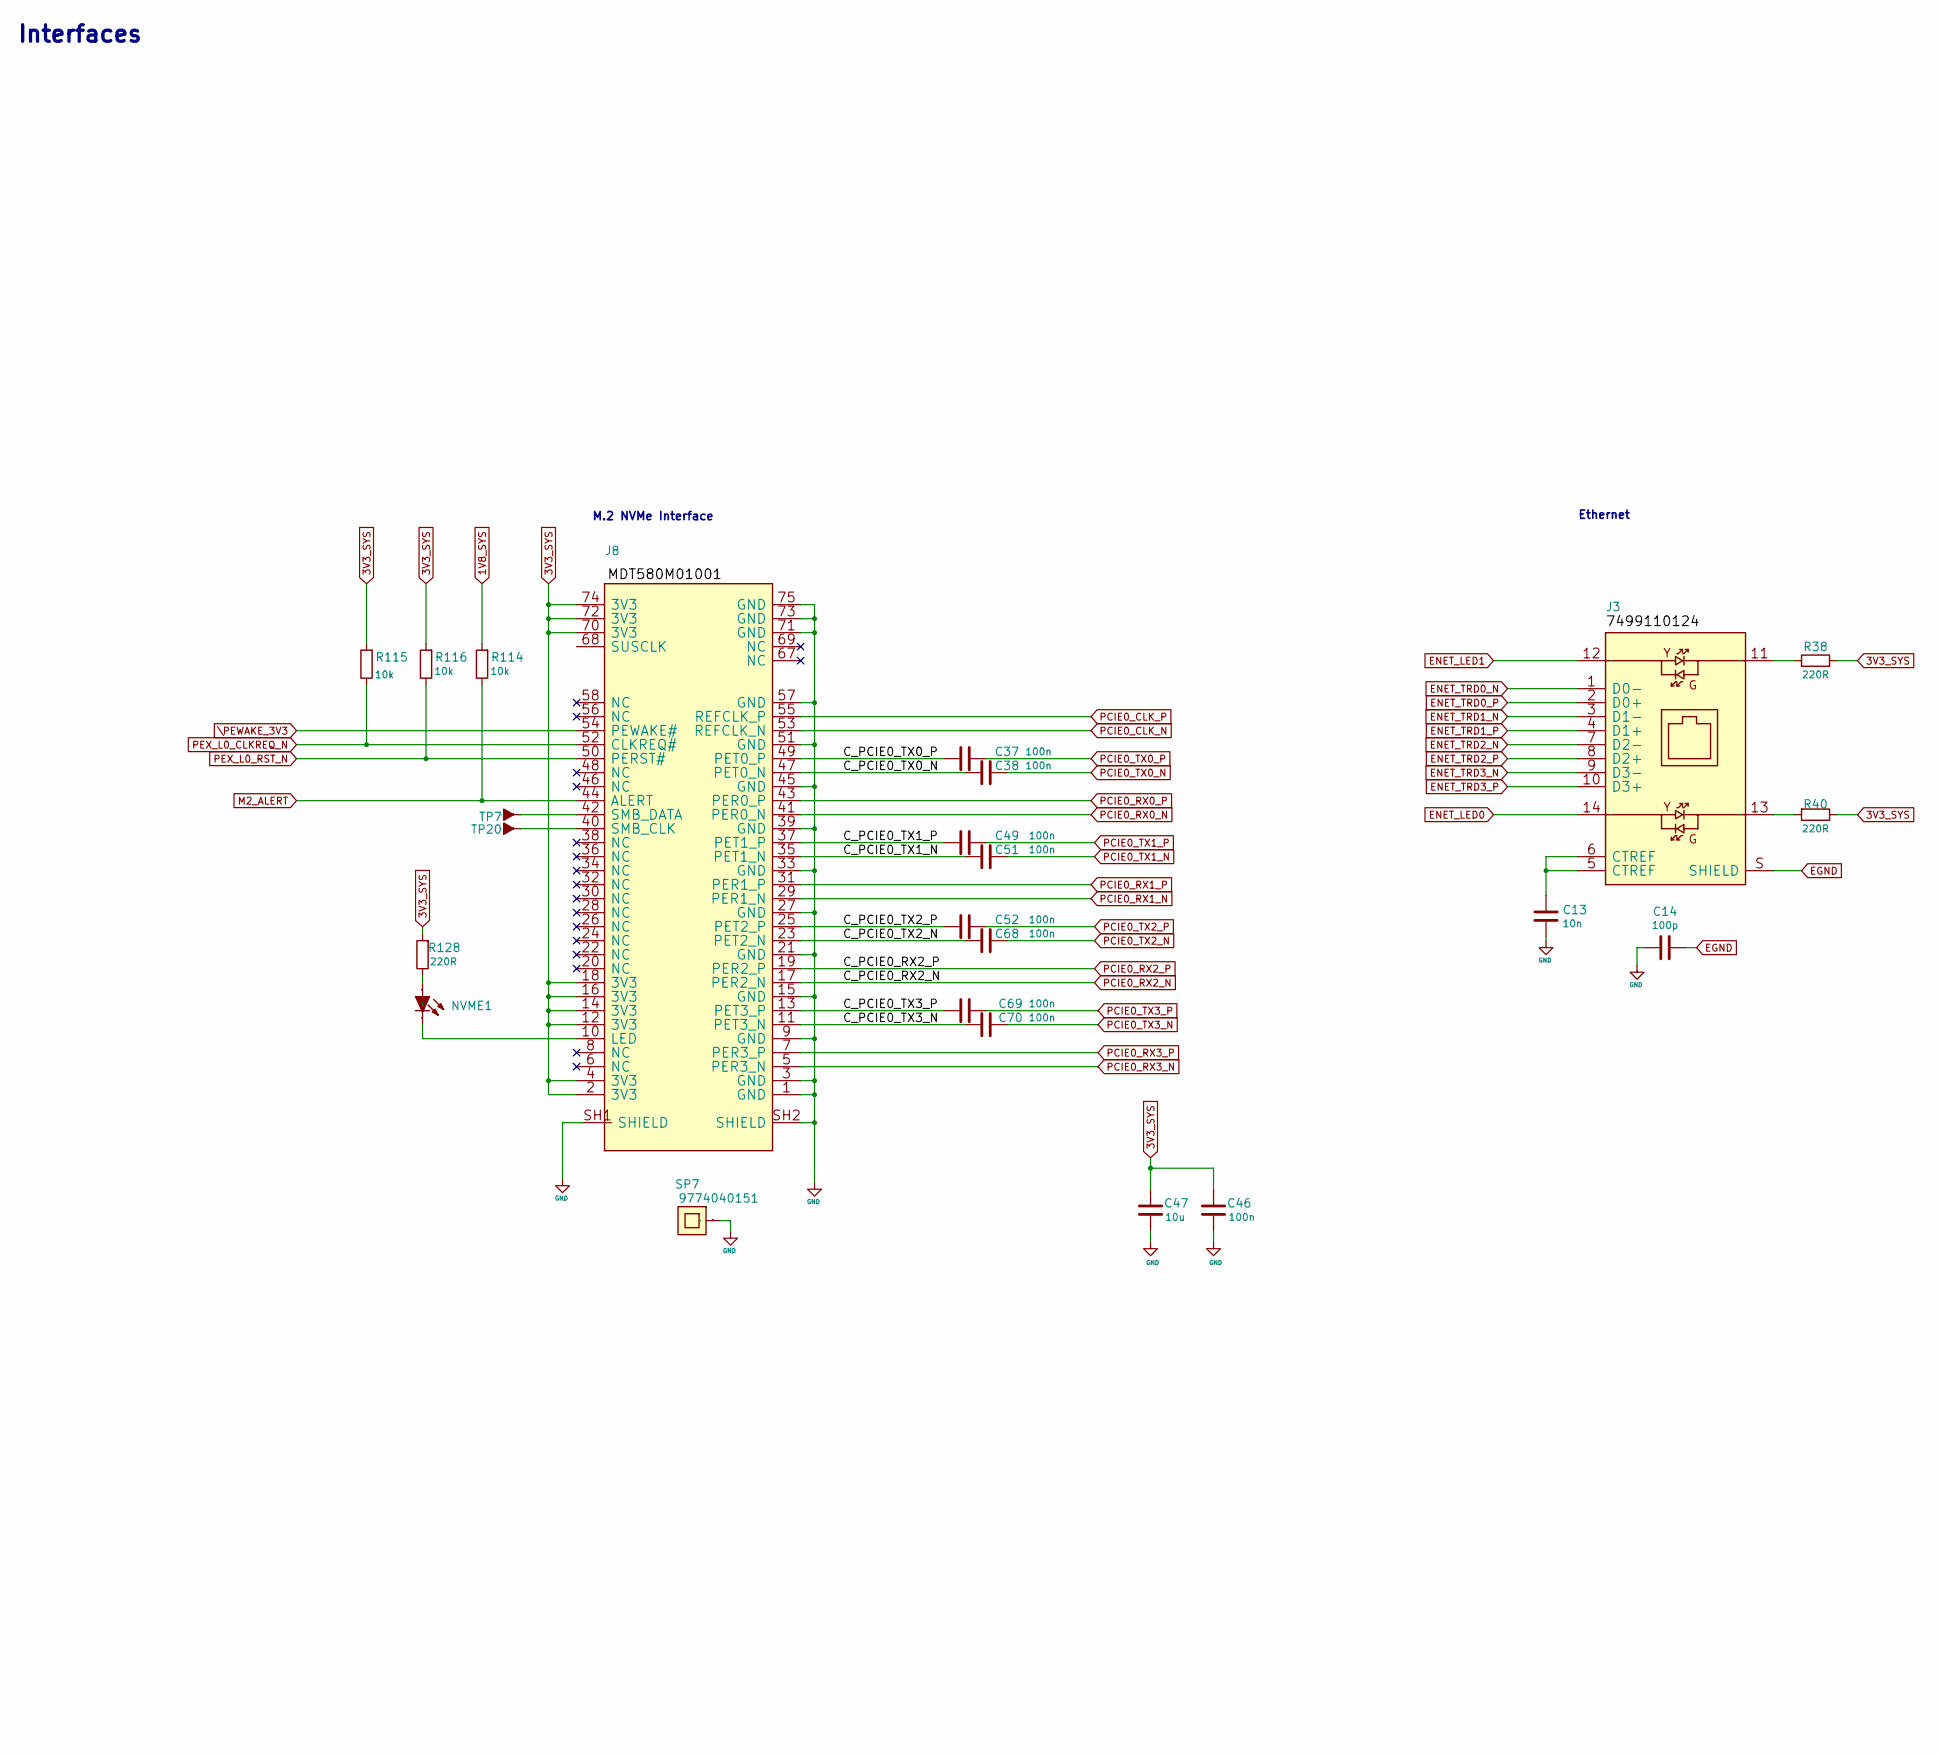
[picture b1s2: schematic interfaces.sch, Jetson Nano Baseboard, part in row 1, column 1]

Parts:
C13: C_10n_0402; 0402-cap; MPN 04025G103ZAT2A
C14: C_100p_0402; 0402-cap; MPN 0402N101J500CT
C37, C38, C46, C49, C51, C52, C68, C69, C70: C_100n_0402; 0402-cap; MPN 0402X104K6R3CT
C47: C_10u_0603; 0603-cap; MPN GRM188R61A106KE69D
J3: WE_7499110124; PartSymbol 7499110124
J8: MDT580M01001; MPN MDT580M01001
NVME1: LED0603; MPN KPT-1608SGC
R38, R40, R128: R_220R_0402; 0402-res; MPN ERJ2GEJ221X
R114, R115, R116: R_10k_0402; 0402-res; MPN CRCW040210K0FKEDHP
SP7: 9774040151; M2.5-4mm; MPN 9774040151
TP7, TP20: TP-R-1.5; MPN N/A

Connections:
1V8_SYS: R114.2; also elsewhere on the board
3V3_SYS: C46.2, C47.2, J8.2 (3V3), J8.4 (3V3), J8.12 (3V3), J8.14 (3V3), J8.16 (3V3), J8.18 (3V3), J8.70 (3V3), J8.72 (3V3), J8.74 (3V3), R38.2, R40.1, R115.2, R116.2, R128.2; also elsewhere on the board
/Interfaces/C_PCIE0_TX0_N: C38.1, J8.47 (PET0_N)
/Interfaces/C_PCIE0_TX0_P: C37.1, J8.49 (PET0_P)
/Interfaces/C_PCIE0_TX1_N: C51.1, J8.35 (PET1_N)
/Interfaces/C_PCIE0_TX1_P: C49.1, J8.37 (PET1_P)
/Interfaces/C_PCIE0_TX2_N: C68.1, J8.23 (PET2_N)
/Interfaces/C_PCIE0_TX2_P: C52.1, J8.25 (PET2_P)
/Interfaces/C_PCIE0_TX3_N: C70.1, J8.11 (PET3_N)
/Interfaces/C_PCIE0_TX3_P: C69.1, J8.13 (PET3_P)
EGND: C14.1, J3.S (SHIELD); also elsewhere on the board
ENET_LED0: J3.14; also elsewhere on the board
ENET_LED1: J3.12; also elsewhere on the board
ENET_TRD0_N: J3.1 (D0-); also elsewhere on the board
ENET_TRD0_P: J3.2 (D0+); also elsewhere on the board
ENET_TRD1_N: J3.3 (D1-); also elsewhere on the board
ENET_TRD1_P: J3.4 (D1+); also elsewhere on the board
ENET_TRD2_N: J3.7 (D2-); also elsewhere on the board
ENET_TRD2_P: J3.8 (D2+); also elsewhere on the board
ENET_TRD3_N: J3.9 (D3-); also elsewhere on the board
ENET_TRD3_P: J3.10 (D3+); also elsewhere on the board
M2_ALERT: J8.44 (ALERT), R114.1; also elsewhere on the board
unnamed: C13.1, J3.5 (CTREF), J3.6 (CTREF)
unnamed: J3.11, R38.1
unnamed: J3.13, R40.2
unnamed: J8.10 (LED), NVME1.K
unnamed: J8.40 (SMB_CLK), TP20.1
unnamed: J8.42 (SMB_DATA), TP7.1
unnamed: NVME1.A, R128.1
PCIE0_CLK_N: J8.53 (REFCLK_N); also elsewhere on the board
PCIE0_CLK_P: J8.55 (REFCLK_P); also elsewhere on the board
PCIE0_RX0_N: J8.41 (PER0_N); also elsewhere on the board
PCIE0_RX0_P: J8.43 (PER0_P); also elsewhere on the board
PCIE0_RX1_N: J8.29 (PER1_N); also elsewhere on the board
PCIE0_RX1_P: J8.31 (PER1_P); also elsewhere on the board
PCIE0_RX2_N: J8.17 (PER2_N); also elsewhere on the board
PCIE0_RX2_P: J8.19 (PER2_P); also elsewhere on the board
PCIE0_RX3_N: J8.5 (PER3_N); also elsewhere on the board
PCIE0_RX3_P: J8.7 (PER3_P); also elsewhere on the board
PCIE0_TX0_N: C38.2; also elsewhere on the board
PCIE0_TX0_P: C37.2; also elsewhere on the board
PCIE0_TX1_N: C51.2; also elsewhere on the board
PCIE0_TX1_P: C49.2; also elsewhere on the board
PCIE0_TX2_N: C68.2; also elsewhere on the board
PCIE0_TX2_P: C52.2; also elsewhere on the board
PCIE0_TX3_N: C70.2; also elsewhere on the board
PCIE0_TX3_P: C69.2; also elsewhere on the board
PEX_L0_CLKREQ_N: J8.52 (CLKREQ#), R115.1; also elsewhere on the board
PEX_L0_RST_N: J8.50 (PERST#), R116.1; also elsewhere on the board
\PEWAKE_3V3: J8.54 (PEWAKE#); also elsewhere on the board

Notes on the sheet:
Text
Ethernet
M.2 NVMe Interface
Interfaces

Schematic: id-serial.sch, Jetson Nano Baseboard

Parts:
C36: C_100n_0402; 0402-cap; MPN 0402X104K6R3CT
D15: diode; SOD-323; MPN 1N4148WS
IC17: AT24CS01-ST; SOT23-5; MPN AT24CS01-ST
R132: R_0R_0402; 0402-res; MPN ERJ2GE0R00X
TP30: TC2030; MPN TC2030

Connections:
3V3_SYS: C36.2, D15.A; also elsewhere on the board
/ID Serial/EEPROM_PWR: D15.C, IC17.4 (VCC), TP30.1 (VCC/VCCIO)
/ID Serial/SN_WP: IC17.5 (WP), R132.1
GEN0_SCL: IC17.1 (SCL), TP30.4 (TXD/TCLK); also elsewhere on the board
GEN0_SDA: IC17.3 (SDA), TP30.3 (RXD/TDI), TP30.6 (RTS/TDO); also elsewhere on the board
unnamed: R132.2, TP30.2 (CTS/TMS)

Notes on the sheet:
Text
EEPROM with Unique ID
0x58h - SN
I2C address:
0x50h - memory
ID serial
